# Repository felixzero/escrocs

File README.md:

# Repository of the E.S.C.Ro.C.S. team at the French robotics cup

We have participated in 2020, 2021 and 2022.

You can find here our codes, PCB and mechanical designs. We use Platform.io and VSCodium for coding, KiCAD for PCB CAD and either FreeCAD or TinkerCAD for mechanical design.

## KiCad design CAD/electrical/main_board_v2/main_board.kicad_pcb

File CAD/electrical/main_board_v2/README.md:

# Main board

This is the brain of our robots. It is based on a single ESP32 chip executing the strategy and interfacing with other boards.

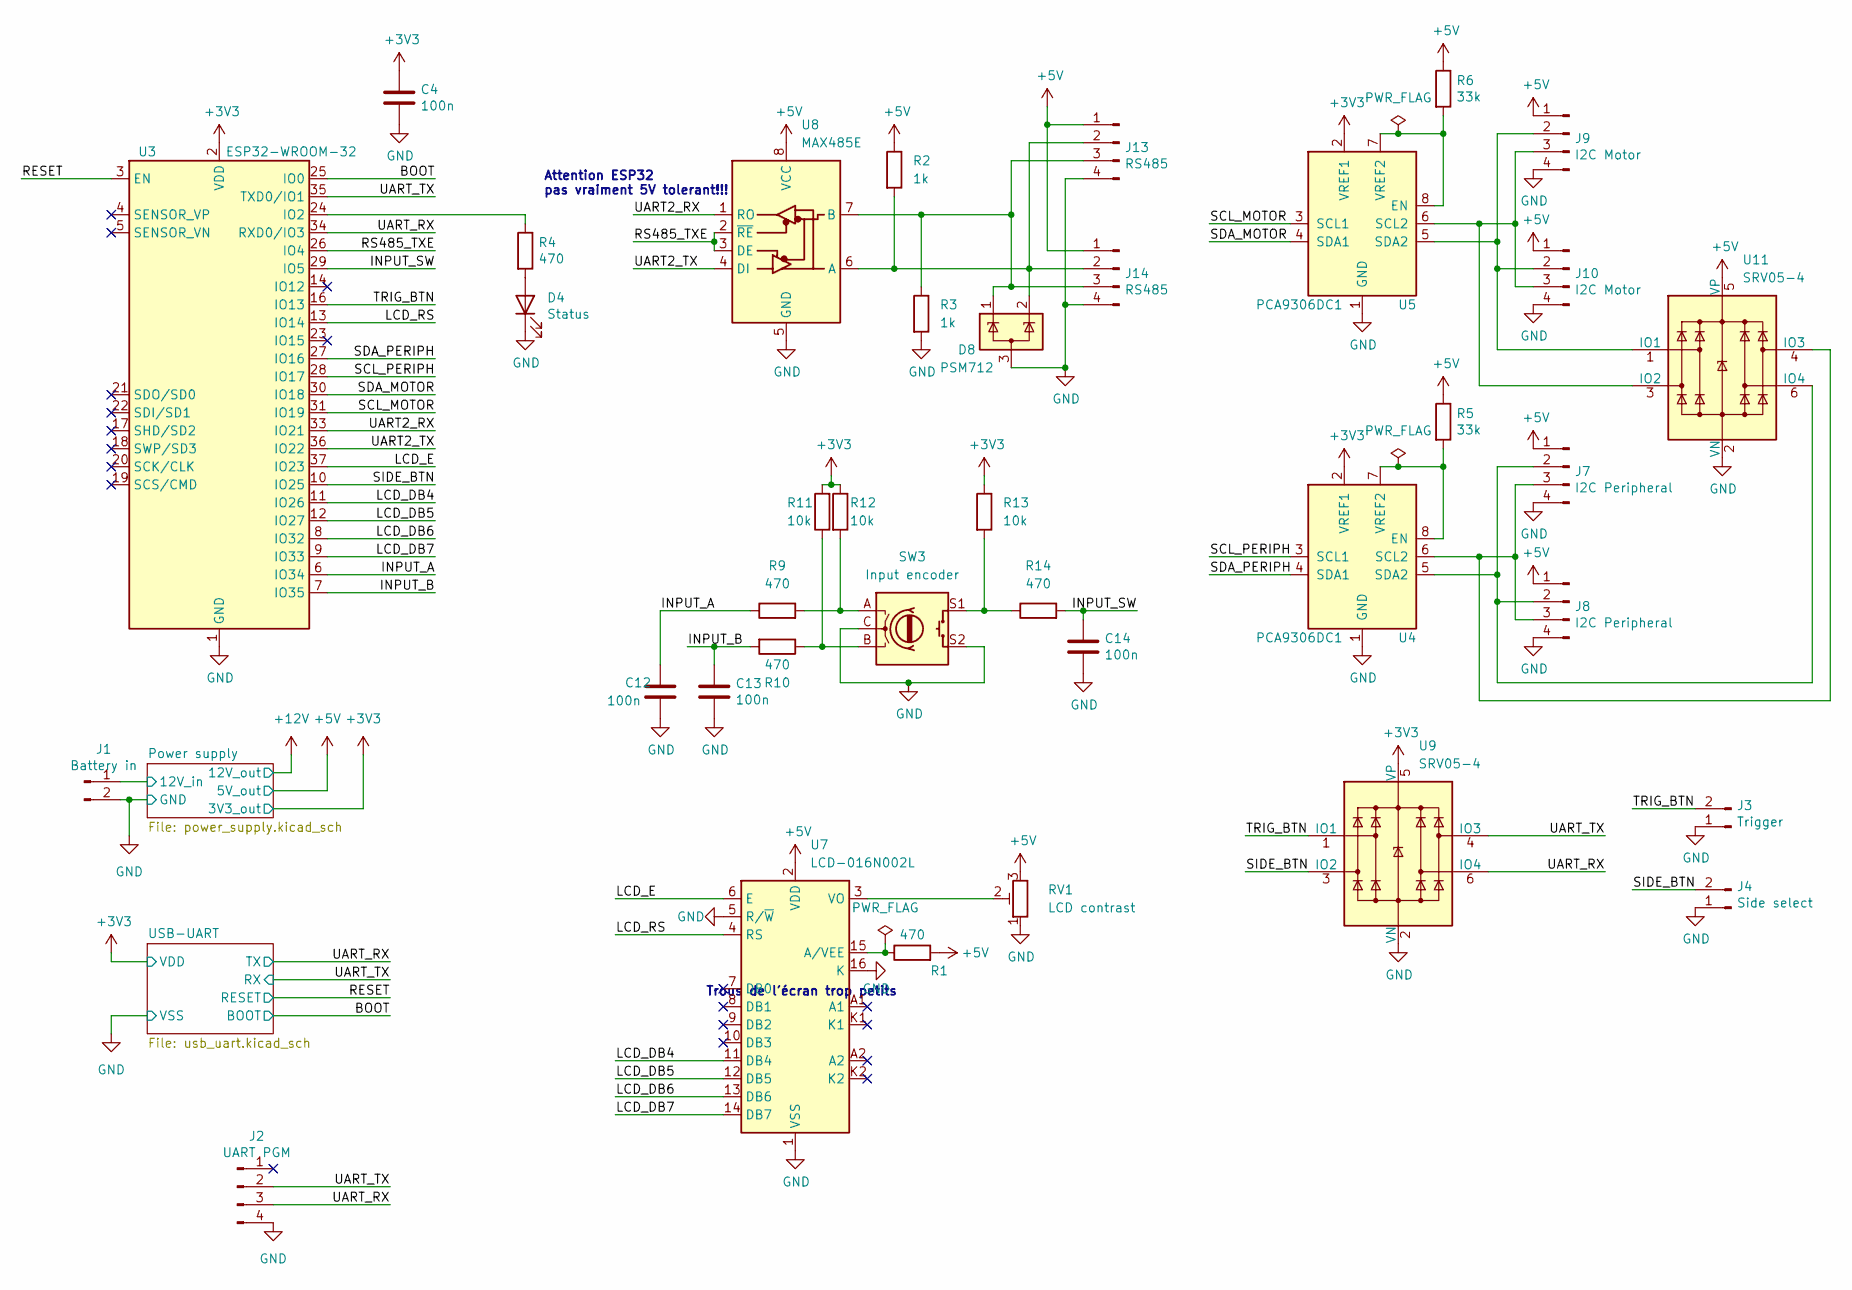
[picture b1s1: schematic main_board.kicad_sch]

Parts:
C4, C12, C13, C14: 100n; C_0805_2012Metric; LCSC C28233
D4: Status; LED_0603_1608Metric; LCSC C2286
D8: PSM712; SOT-23
J1: Battery in; BarrelJack_Horizontal
J2: UART PGM; Molex_KK-254_AE-6410-04A_1x04_P2.54mm_Vertical
J3: Trigger; Molex_KK-254_AE-6410-02A_1x02_P2.54mm_Vertical
J4: Side select; Molex_KK-254_AE-6410-02A_1x02_P2.54mm_Vertical
J7, J8: I2C Peripheral; Molex_KK-254_AE-6410-04A_1x04_P2.54mm_Vertical
J9, J10: I2C Motor; Molex_KK-254_AE-6410-04A_1x04_P2.54mm_Vertical
J13, J14: RS485; Molex_KK-254_AE-6410-04A_1x04_P2.54mm_Vertical
R1: 470; R_1206_3216Metric
R2: 1k; R_0603_1608Metric; LCSC C20190
R3: 1k; R_0603_1608Metric; LCSC C20192
R4: 470; R_1206_3216Metric; LCSC C17901
R5, R6: 33k; R_0603_1608Metric; LCSC C17900
R9, R10, R14: 470; R_0603_1608Metric
R11, R12, R13: 10k; R_0603_1608Metric
RV1: LCD contrast; Potentiometer_Bourns_3314J_Vertical
SW3: Input encoder; RotaryEncoder_Alps_EC11E-Switch_Vertical_H20mm
U3: ESP32-WROOM-32; ESP32-WROOM-32U; LCSC C82899
U4, U5: PCA9306DC1; VSSOP-8_2.3x2mm_P0.5mm
U7: LCD-016N002L; WC1602A
U8: MAX485E; SOIC-8_3.9x4.9mm_P1.27mm
U9, U11: SRV05-4; SOT-23-6

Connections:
+3V3: C4.1, R11.2, R12.1, R13.1, U3.2 (VDD), U4.2 (VREF1), U5.2 (VREF1), U9.5 (VP); also elsewhere on the board
+5V: J7.1, J8.1, J9.1, J10.1, J13.1, J14.1, R1.2, R2.1, R5.1, R6.1, RV1.3, U7.2 (VDD), U8.8 (VCC), U11.5 (VP); also elsewhere on the board
/BOOT: U3.25 (IO0); also elsewhere on the board
/INPUT_A: C12.1, R9.1, U3.6 (IO34)
/INPUT_B: C13.1, R10.2, U3.7 (IO35)
/INPUT_SW: C14.1, R14.2, U3.29 (IO5)
/LCD_DB4: U3.11 (IO26), U7.11 (DB4)
/LCD_DB5: U3.12 (IO27), U7.12 (DB5)
/LCD_DB6: U3.8 (IO32), U7.13 (DB6)
/LCD_DB7: U3.9 (IO33), U7.14 (DB7)
/LCD_E: U3.37 (IO23), U7.6 (E)
/LCD_RS: U3.13 (IO14), U7.4 (RS)
/Power supply/12V_in: J1.1; also elsewhere on the board
/RESET: U3.3 (EN); also elsewhere on the board
/RS485_TXE: U3.26 (IO4), U8.2 (~RE), U8.3 (DE)
/SCL_MOTOR: U3.31 (IO19), U5.3 (SCL1)
/SCL_PERIPH: U3.28 (IO17), U4.3 (SCL1)
/SDA_MOTOR: U3.30 (IO18), U5.4 (SDA1)
/SDA_PERIPH: U3.27 (IO16), U4.4 (SDA1)
/SIDE_BTN: J4.2, U3.10 (IO25), U9.3 (IO2)
/TRIG_BTN: J3.2, U3.16 (IO13), U9.1 (IO1)
/UART2_RX: U3.33 (IO21), U8.1 (RO)
/UART2_TX: U3.36 (IO22), U8.4 (DI)
/UART_RX: J2.3, U3.34 (RXD0/IO3), U9.6 (IO4); also elsewhere on the board
/UART_TX: J2.2, U3.35 (TXD0/IO1), U9.4 (IO3); also elsewhere on the board
GND: C4.2, C12.2, C13.2, C14.2, D4.1 (K), D8.3 (A), J1.2, J2.4, J3.1, J4.1, J7.4, J8.4, J9.4, J10.4, J13.4, J14.4, R3.2, RV1.1, SW3.C, SW3.S2, U3.1 (GND), U3.15 (GND), U3.38 (GND), U3.39 (GND), U4.1 (GND), U5.1 (GND), U7.1 (VSS), U7.5 (R/~W), U7.16 (K), U8.5 (GND), U9.2 (VN), U11.2 (VN); also elsewhere on the board
unnamed: D4.2 (A), R4.2
unnamed: J7.2, J8.2, U4.5 (SDA2), U11.6 (IO4)
unnamed: J7.3, J8.3, U4.6 (SCL2), U11.4 (IO3)
unnamed: J9.2, J10.2, U5.5 (SDA2), U11.1 (IO1)
unnamed: J9.3, J10.3, U5.6 (SCL2), U11.3 (IO2)
unnamed: R1.1, U7.15 (A/VEE)
unnamed: R4.1, U3.24 (IO2)
unnamed: R5.2, U4.7 (VREF2), U4.8 (EN)
unnamed: R6.2, U5.7 (VREF2), U5.8 (EN)
unnamed: R10.1, R11.1, SW3.B
unnamed: R9.2, R12.2, SW3.A
unnamed: R13.2, R14.1, SW3.S1
unnamed: RV1.2, U7.3 (VO)
unnamed: D8.2 (K), J13.2, J14.2, R2.2, U8.6 (A)
unnamed: D8.1 (K), J13.3, J14.3, R3.1, U8.7 (B)

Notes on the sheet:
Attention ESP32 pas vraiment 5V tolerant!!!
Trous de l'écran trop petits

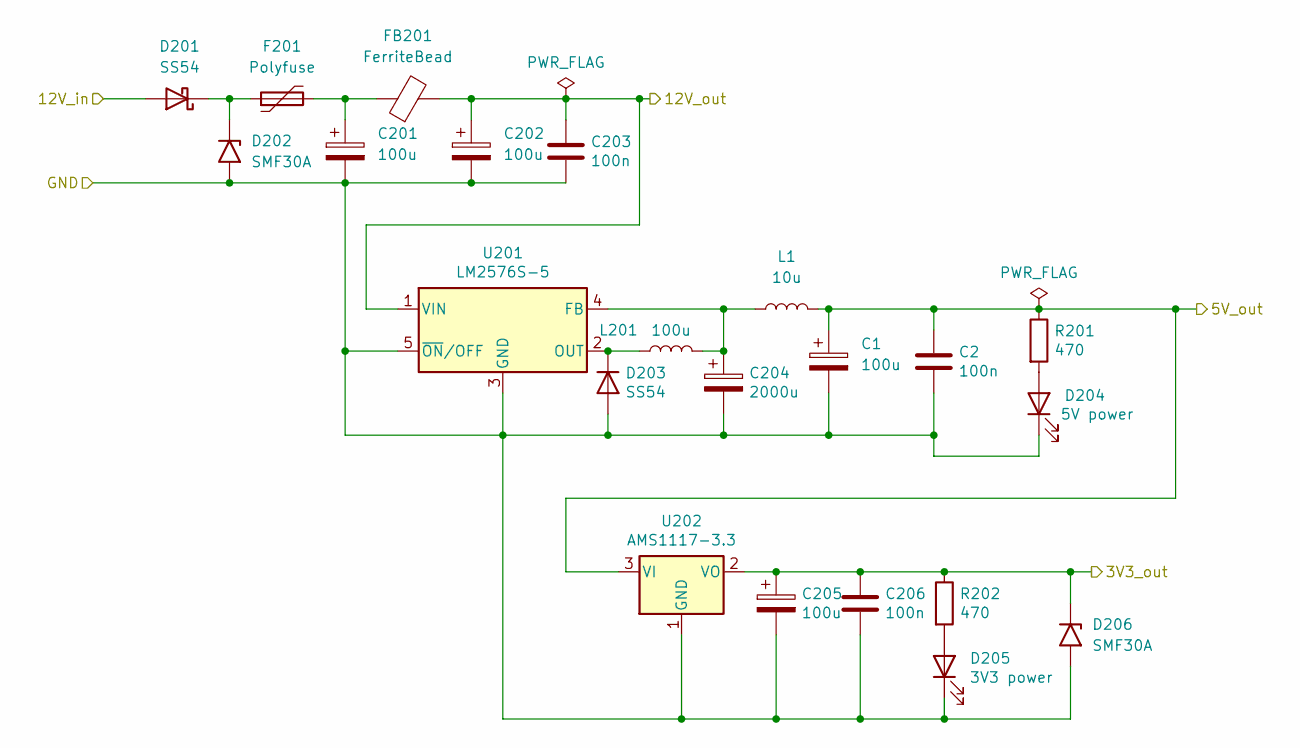
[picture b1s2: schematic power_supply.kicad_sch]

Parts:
C1, C201, C202, C205: 100u; CP_Elec_8x10; LCSC C16133
C2, C203, C206: 100n; C_0805_2012Metric; LCSC C28233
C204: 2000u; CP_Elec_10x10.5; LCSC C10752
D201: SS54; D_SMA
D202, D206: SMF30A; D_SMF; LCSC C19077518
D203: SS54; D_SMA; LCSC C22452
D204: 5V power; LED_0603_1608Metric; LCSC C2286
D205: 3V3 power; LED_0603_1608Metric; LCSC C2286
F201: Polyfuse; Fuse_1812_4532Metric
FB201: FerriteBead; L_0805_2012Metric
L1: 10u; L_12x12mm_H6mm
L201: 100u; L_12x12mm_H6mm; LCSC C169378
R201: 470; R_1206_3216Metric; LCSC C17887
R202: 470; R_1206_3216Metric; LCSC C17901
U201: LM2576S-5; TO-263-5_TabPin3; LCSC C34465
U202: AMS1117-3.3; SOT-223-3_TabPin2; LCSC C6186

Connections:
+3V3: C205.1, C206.1, D206.1 (A1), R202.1, U202.2 (VO); also elsewhere on the board
+5V: C1.1, C2.1, L1.2, R201.1, U202.3 (VI); also elsewhere on the board
+12V: C202.1, C203.1, FB201.2, U201.1 (VIN)
/Power supply/12V_in: D201.2 (A); also elsewhere on the board
GND: C1.2, C2.2, C201.2, C202.2, C203.2, C204.2, C205.2, C206.2, D202.2 (A2), D203.2 (A), D204.1 (K), D205.1 (K), D206.2 (A2), U201.3 (GND), U201.5 (~ON/OFF), U202.1 (GND); also elsewhere on the board
unnamed: C201.1, F201.2, FB201.1
unnamed: C204.1, L1.1, L201.2, U201.4 (FB)
unnamed: D201.1 (K), D202.1 (A1), F201.1
unnamed: D203.1 (K), L201.1, U201.2 (OUT)
unnamed: D204.2 (A), R201.2
unnamed: D205.2 (A), R202.2

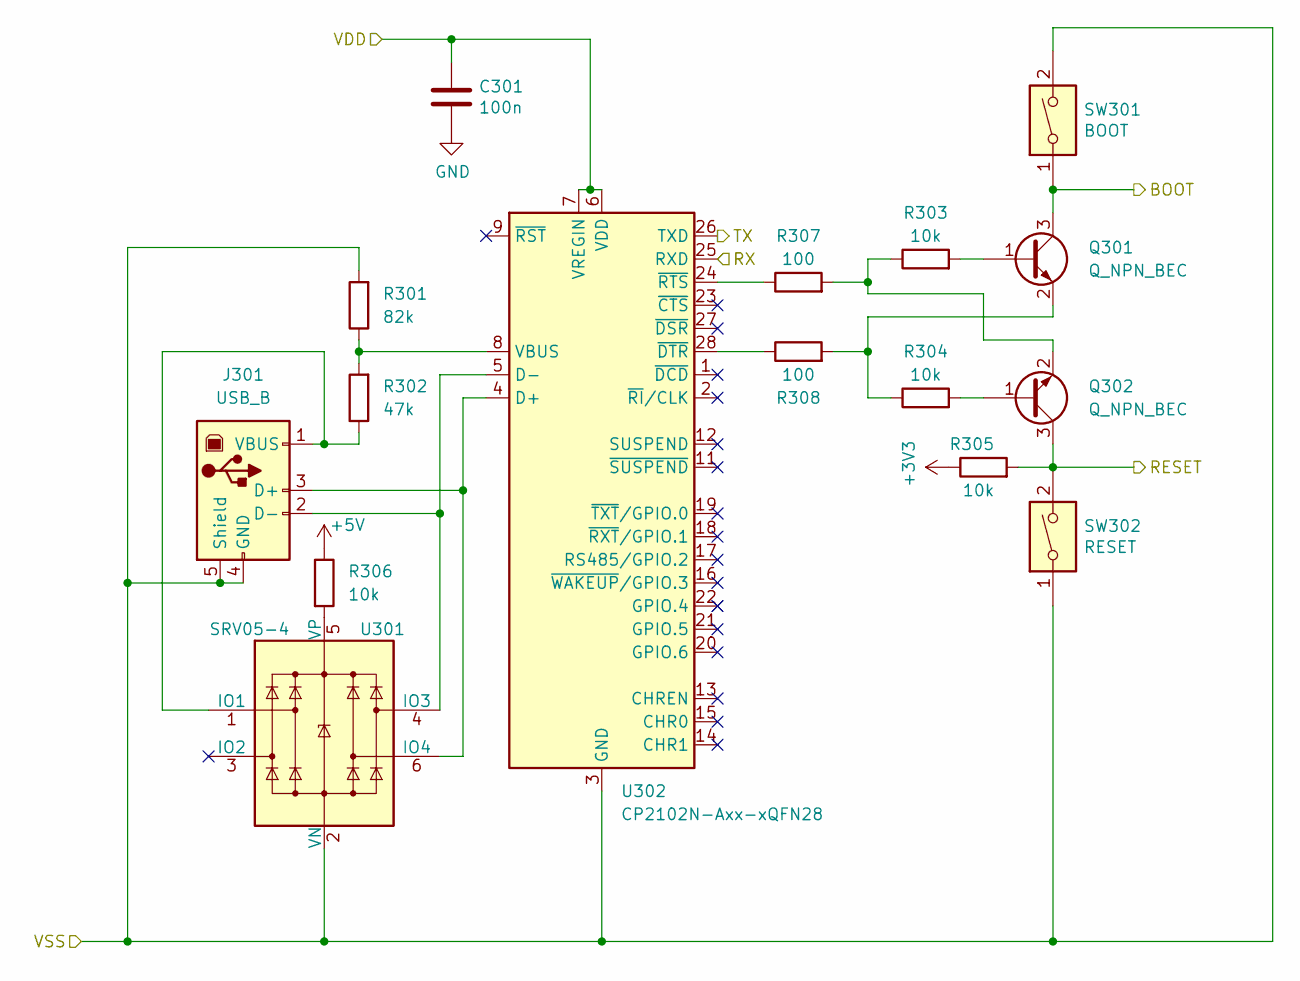
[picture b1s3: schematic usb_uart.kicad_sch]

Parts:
C301: 100n; C_0805_2012Metric; LCSC C28233
J301: USB_B; USB_B_TE_5787834_Vertical
Q301, Q302: Q_NPN_BEC; SOT-23
R301: 82k; R_0603_1608Metric
R302: 47k; R_0603_1608Metric
R303, R304, R306: 10k; R_0603_1608Metric
R305: 10k; R_0603_1608Metric; LCSC C17902
R307, R308: 100; R_0603_1608Metric; LCSC C22775
SW301: BOOT; SW_Push_1P1T_NO_6x6mm_H9.5mm
SW302: RESET; SW_Push_1P1T_NO_6x6mm_H9.5mm
U301: SRV05-4; SOT-23-6
U302: CP2102N-Axx-xQFN28; QFN-28-1EP_5x5mm_P0.5mm_EP3.35x3.35mm

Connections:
+3V3: C301.1, R305.1, U302.6 (VDD), U302.7 (VREGIN); also elsewhere on the board
+5V: R306.1; also elsewhere on the board
/BOOT: Q301.3 (C), SW301.1; also elsewhere on the board
/RESET: Q302.3 (C), R305.2, SW302.2; also elsewhere on the board
/UART_RX: U302.26 (TXD); also elsewhere on the board
/UART_TX: U302.25 (RXD); also elsewhere on the board
GND: C301.2, J301.4 (GND), J301.5 (Shield), R301.2, SW301.2, SW302.1, U301.2 (VN), U302.3 (GND), U302.29 (GND); also elsewhere on the board
unnamed: J301.1 (VBUS), R302.1, U301.1 (IO1)
unnamed: J301.2 (D-), U301.4 (IO3), U302.5 (D-)
unnamed: J301.3 (D+), U301.6 (IO4), U302.4 (D+)
unnamed: Q301.1 (B), R303.2
unnamed: Q301.2 (E), R304.1, R308.2
unnamed: Q302.1 (B), R304.2
unnamed: Q302.2 (E), R303.1, R307.2
unnamed: R301.1, R302.2, U302.8 (VBUS)
unnamed: R306.2, U301.5 (VP)
unnamed: R307.1, U302.24 (~RTS)
unnamed: R308.1, U302.28 (~DTR)

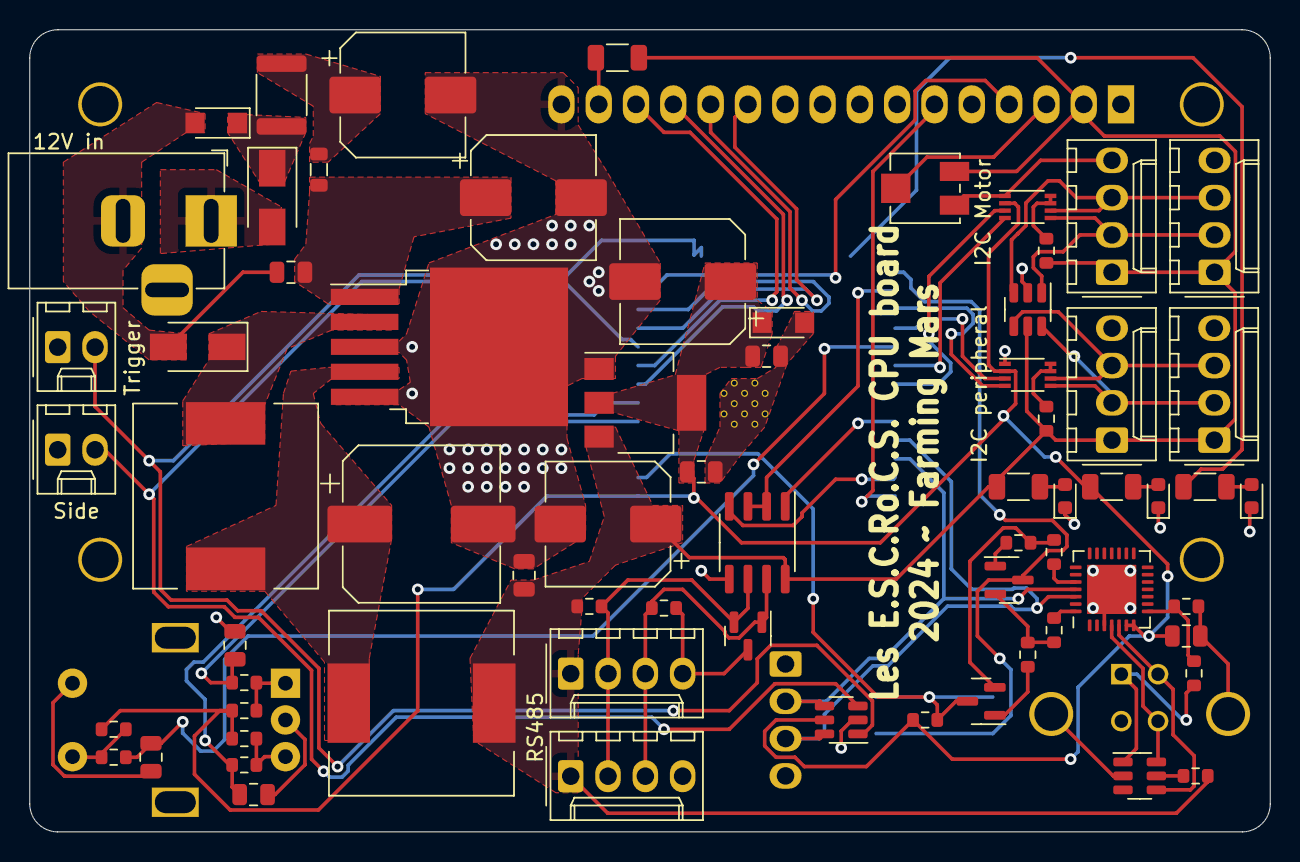
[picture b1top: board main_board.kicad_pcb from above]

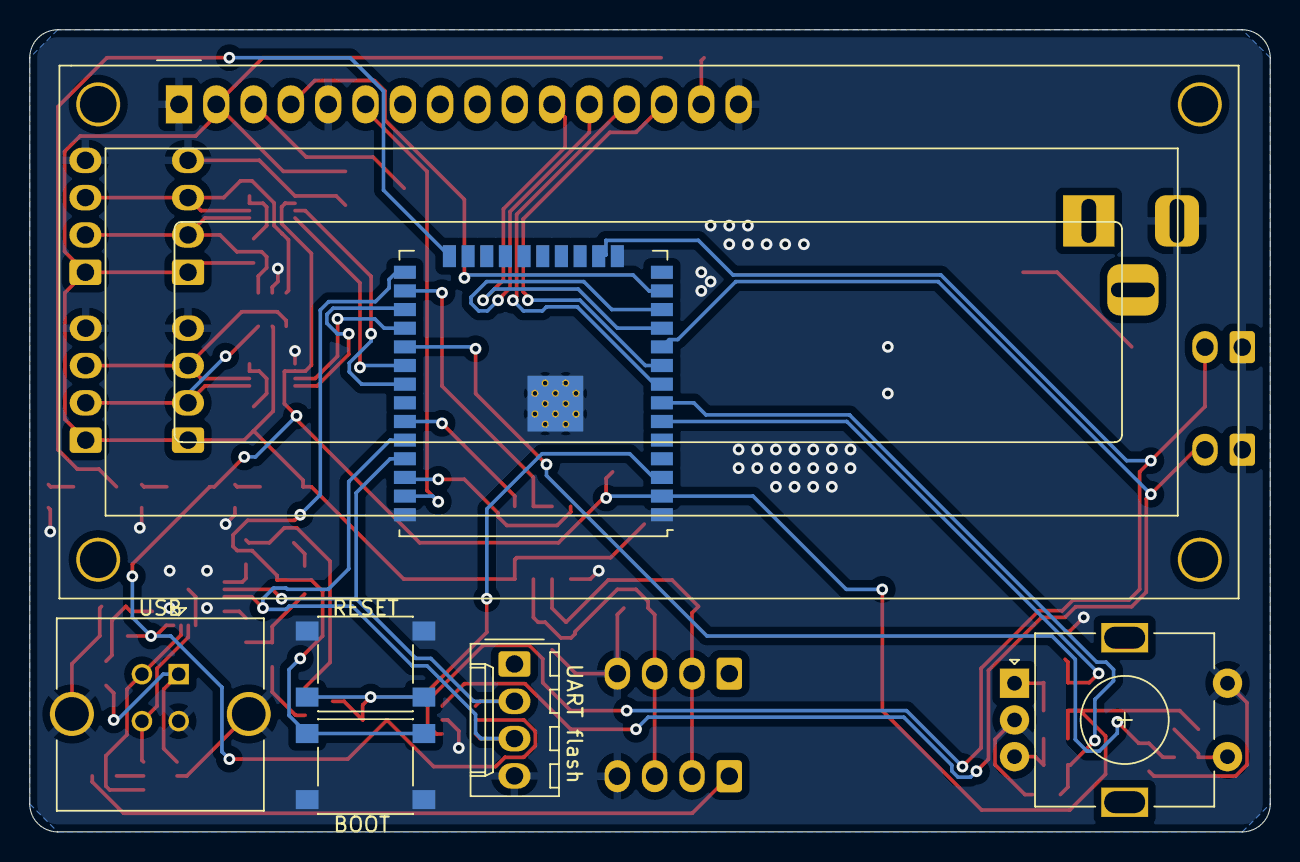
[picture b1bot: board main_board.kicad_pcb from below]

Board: 2 copper layers, 84.5 x 54.6 mm, 75 parts (7 on the bottom side), 59 nets.

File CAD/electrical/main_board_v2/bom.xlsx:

Comment | Designator | Footprint | LCSC part number
100n capacitor | C2,C4,C12,C13,C14,C203,C206,C301 | Capacitor_SMD:C_0805_2012Metric | C28233
100u capacitor | C1,C201,C202,C205 | Capacitor_SMD:CP_Elec_8x10 | C294509
2000u capacitor | C204 | Capacitor_SMD:CP_Elec_10x10.5 | C336751
LED | D4,D204,D205 | LED_SMD:LED_0603_1608Metric | C72038
PSM712 | D8 | Package_TO_SOT_SMD:SOT-23 | C32677
SS54 | D201,D203 | Diode_SMD:D_SMA | C22452
SMF30A | D202,D206 | Diode_SMD:D_SMF | C2990493
Polyfuse RF1404-000 | F201 | Fuse:Fuse_1812_4532Metric | C3107
GZ2012D601TF | FB201 | Inductor_SMD:L_0805_2012Metric | C1017
100u inductor | L201 | Inductor_SMD:L_12x12mm_H6mm | C169378
10u inductor | L1 | Inductor_SMD:L_12x12mm_H6mm | C9904
Basic NPN | Q301,Q302 | Package_TO_SOT_SMD:SOT-23 | C20526
470 resistor | R1,R4,R201,R202,R9,R10,R14 | Resistor_SMD:R_1206_3216Metric | C23179
33k resistor | R5,R6 | Resistor_SMD:R_0603_1608Metric | C4216
10k resistor | R11,R12,R13,R303,R304,R305,R306 | Resistor_SMD:R_0603_1608Metric | C25804
82k resistor | R301 | Resistor_SMD:R_0603_1608Metric | C23254
47k resistor | R302 | Resistor_SMD:R_0603_1608Metric | C25819
100 resistor | R307,R308 | Resistor_SMD:R_0603_1608Metric | C22775
1k resistor | R2,R3 | Resistor_SMD:R_0603_1608Metric | C22775
PCA9306DC | U4,U5 | Package_SO:VSSOP-8_2.3x2mm_P0.5mm | C129510
SN75176BDR | U8 | Package_SO:SOIC-8_3.9x4.9mm_P1.27mm | C7063
SRV05-4 | U9,U11,U301 | Package_TO_SOT_SMD:SOT-23-6 | C85364
LM2576S-5 | U201 | Package_TO_SOT_SMD:TO-263-5_TabPin3 | C34465
AMS1117-3.3 | U202 | Package_TO_SOT_SMD:SOT-223-3_TabPin2 | C6186
CP2102 | U302 | Package_DFN_QFN:QFN-28-1EP_5x5mm_P0.5mm_EP3.35x3.35mm | C6568
2kO potentiometer | RV1 | Potentiometer_SMD:Potentiometer_Bourns_3314J_Vertical | C94513

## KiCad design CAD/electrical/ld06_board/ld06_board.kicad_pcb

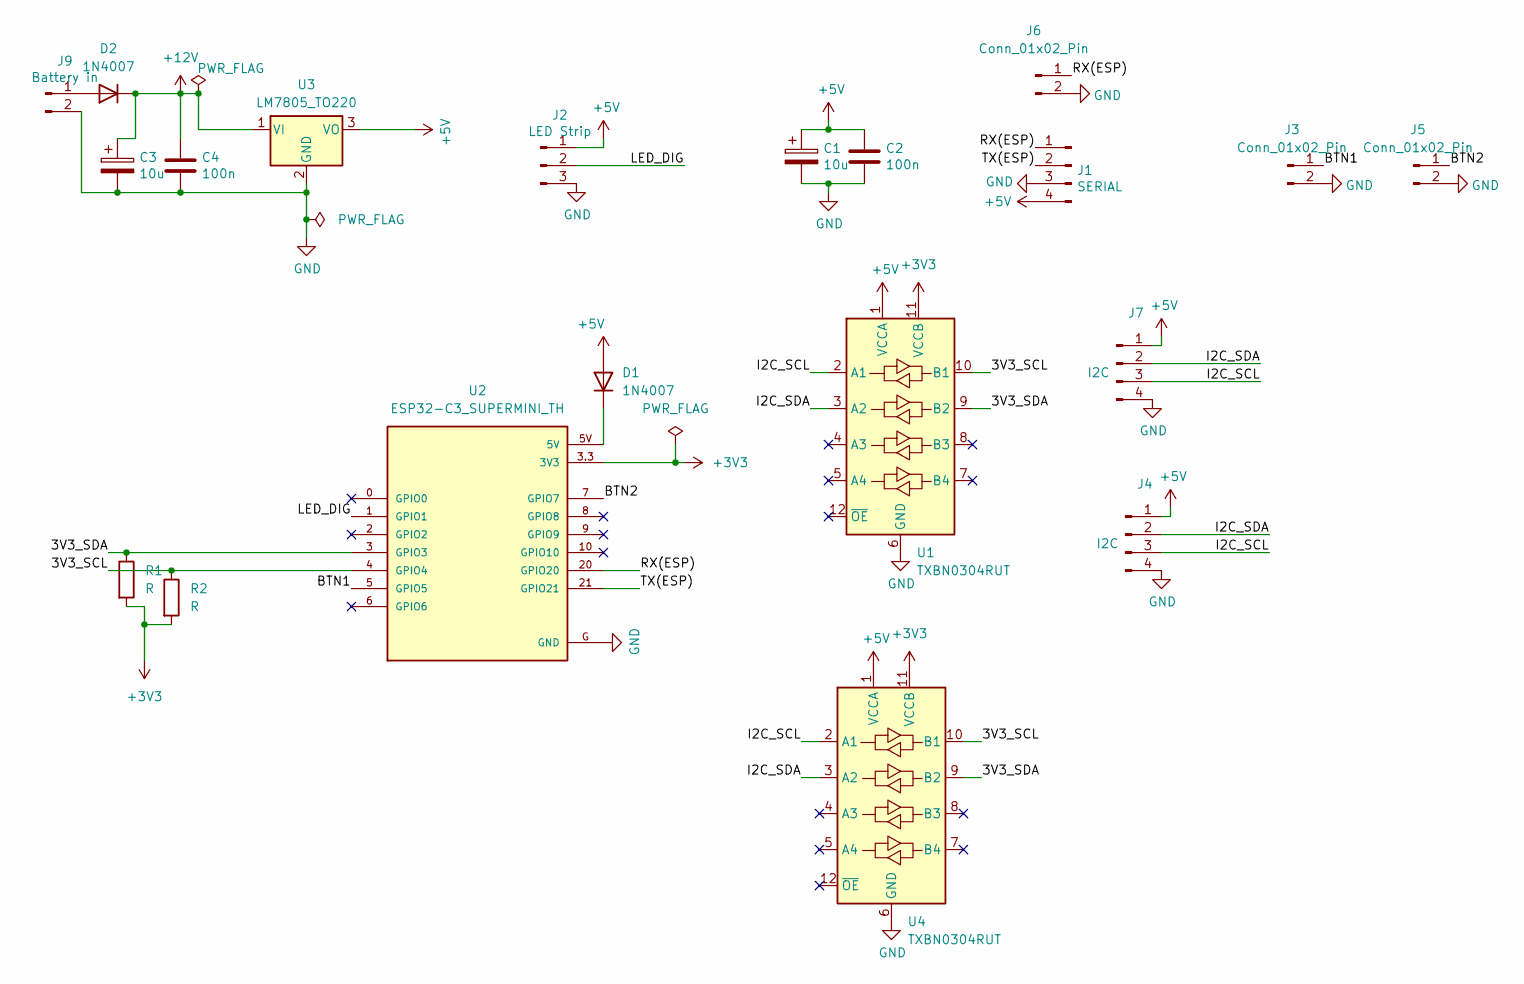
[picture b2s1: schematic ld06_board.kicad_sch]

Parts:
C1, C3: 10u; CP_Radial_D8.0mm_P3.80mm
C2, C4: 100n; R_Axial_DIN0204_L3.6mm_D1.6mm_P5.08mm_Vertical
D1, D2: 1N4007; D_T-1_P12.70mm_Horizontal
J1: SERIAL; Molex_KK-254_AE-6410-04A_1x04_P2.54mm_Vertical
J2: LED Strip; Molex_KK-254_AE-6410-03A_1x03_P2.54mm_Vertical
J3, J5, J6: Conn_01x02_Pin; Molex_KK-254_AE-6410-02A_1x02_P2.54mm_Vertical
J4, J7: I2C; Molex_KK-254_AE-6410-04A_1x04_P2.54mm_Vertical
J9: Battery in; BarrelJack_Horizontal
R1, R2: R; R_Axial_DIN0309_L9.0mm_D3.2mm_P12.70mm_Horizontal
U1: TXBN0304RUT; I2C_ali_level_shifter
U2: ESP32-C3_SUPERMINI_TH; MODULE_ESP32-C3_SUPERMINI
U3: LM7805_TO220; TO-220-3_Vertical
U4: TXBN0304RUT; PCA9306_ali

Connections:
+3V3: R1.2, R2.2, U1.11 (VCCB), U2.3.3 (3V3), U4.11 (VCCB)
+5V: C1.1, C2.1, D1.2 (A), J1.4, J2.1, J4.1, J7.1, U1.1 (VCCA), U3.3 (VO), U4.1 (VCCA)
+12V: C3.1, C4.1, D2.1 (K), U3.1 (VI)
/3V3_SCL: R2.1, U1.10 (B1), U2.4 (GPIO4), U4.10 (B1)
/3V3_SDA: R1.1, U1.9 (B2), U2.3 (GPIO3), U4.9 (B2)
/BTN1: J3.1, U2.5 (GPIO5); also elsewhere on the board
/BTN2: J5.1, U2.7 (GPIO7); also elsewhere on the board
/I2C_SCL: J4.3, J7.3, U1.2 (A1), U4.2 (A1)
/I2C_SDA: J4.2, J7.2, U1.3 (A2), U4.3 (A2)
/LED_DIG: J2.2, U2.1 (GPIO1)
/RX(ESP): J1.1, J6.1, U2.20 (GPIO20)
/TX(ESP): J1.2, U2.21 (GPIO21)
GND: C1.2, C2.2, C3.2, C4.2, J1.3, J2.3, J3.2, J4.4, J5.2, J6.2, J7.4, J9.2, U1.6 (GND), U2.G (GND), U3.2 (GND), U4.6 (GND); also elsewhere on the board
unnamed: D1.1 (K), U2.5V
unnamed: D2.2 (A), J9.1

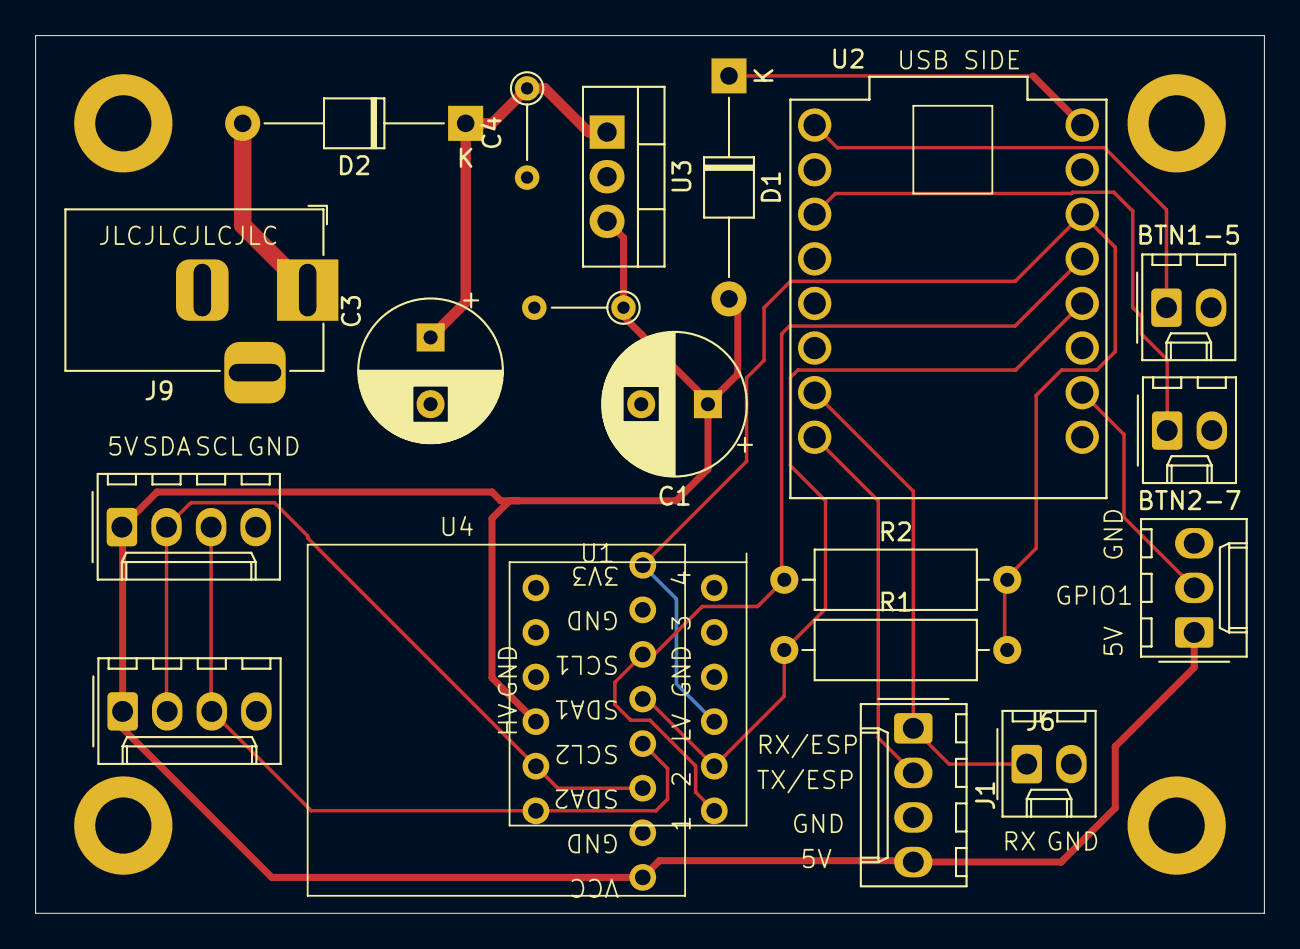
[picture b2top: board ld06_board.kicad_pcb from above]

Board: 2 copper layers, 70.0 x 50.0 mm, 20 parts (0 on the bottom side), 15 nets.

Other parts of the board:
BTN1-5, BTN2-7: Conn_01x02_Pin; Molex_KK-254_AE-6410-02A_1x02_P2.54mm_Vertical

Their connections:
/BTN1: BTN1-5.1; also elsewhere on the board
/BTN2: BTN2-7.1; also elsewhere on the board
GND: BTN1-5.2, BTN2-7.2; also elsewhere on the board

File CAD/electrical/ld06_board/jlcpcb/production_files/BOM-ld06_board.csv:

Comment,Designator,Footprint,LCSC,Quantity
R,R2,R_Axial_DIN0309_L9.0mm_D3.2mm_P12.70mm_Horizontal,,1
TXBN0304RUT,U1,I2C_ali_level_shifter,,1
Conn_01x02_Pin,BTN1-5,Molex_KK-254_AE-6410-02A_1x02_P2.54mm_Vertical,,1
100n,C4,R_Axial_DIN0204_L3.6mm_D1.6mm_P5.08mm_Vertical,,1
Conn_01x02_Pin,BTN2-7,Molex_KK-254_AE-6410-02A_1x02_P2.54mm_Vertical,,1
Conn_01x02_Pin,J6,Molex_KK-254_AE-6410-02A_1x02_P2.54mm_Vertical,,1
SERIAL,J1,Molex_KK-254_AE-6410-04A_1x04_P2.54mm_Vertical,,1
TXBN0304RUT,U4,PCA9306_ali,,1
1N4007,D1,D_T-1_P12.70mm_Horizontal,,1
100n,C2,R_Axial_DIN0204_L3.6mm_D1.6mm_P5.08mm_Vertical,,1
10u,C3,CP_Radial_D8.0mm_P3.80mm,,1
I2C,J4,Molex_KK-254_AE-6410-04A_1x04_P2.54mm_Vertical,,1
ESP32-C3_SUPERMINI_TH,U2,MODULE_ESP32-C3_SUPERMINI,,1
LM7805_TO220,U3,TO-220-3_Vertical,,1
I2C,J7,Molex_KK-254_AE-6410-04A_1x04_P2.54mm_Vertical,,1
LED Strip,J2,Molex_KK-254_AE-6410-03A_1x03_P2.54mm_Vertical,,1
10u,C1,CP_Radial_D8.0mm_P3.80mm,,1
1N4007,D2,D_T-1_P12.70mm_Horizontal,,1
R,R1,R_Axial_DIN0309_L9.0mm_D3.2mm_P12.70mm_Horizontal,,1
Battery in,J9,BarrelJack_Horizontal,,1

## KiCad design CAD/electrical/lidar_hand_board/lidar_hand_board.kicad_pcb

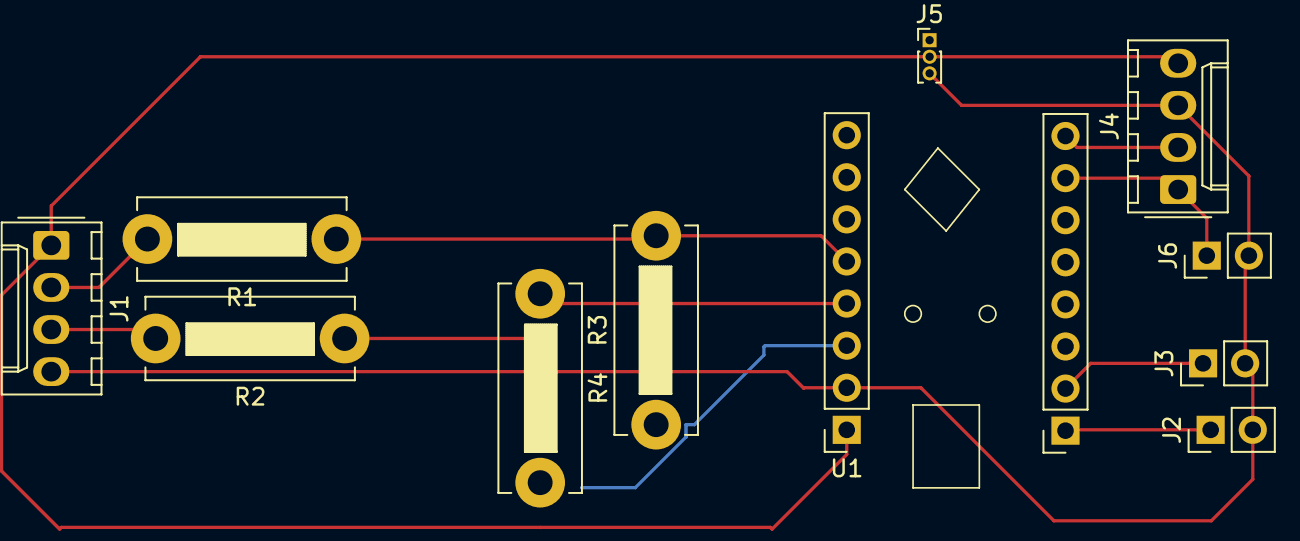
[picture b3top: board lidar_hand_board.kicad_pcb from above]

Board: 2 copper layers, 11 parts (0 on the bottom side), 11 nets.

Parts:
J1: I2C; Molex_KK-254_AE-6410-04A_1x04_P2.54mm_Vertical
J2, J3, J6: Conn_01x02_Pin; PinHeader_1x02_P2.54mm_Vertical
J4: SERIAL; Molex_KK-254_AE-6410-04A_1x04_P2.54mm_Vertical
J5: Conn_01x03_Pin; PinHeader_1x03_P1.00mm_Vertical
R1, R2: 100; R_Bare_Metal_Element_L12.4mm_W4.8mm_P11.40mm
R3, R4: 1000; R_Bare_Metal_Element_L12.4mm_W4.8mm_P11.40mm
U1: ESP32-S3; ESP32_C3_MINI_aproximative_footprint

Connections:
+5V: J1.1, J4.4, J5.2, R3.1, R4.2, U1.2 (VDD3P3)
/BTN1: J2.1, U1.10 (GPIO5)
/BTN2: J3.1, U1.11 (GPIO6)
/LED: J5.1, U1.6 (GPIO1)
/RX(ESP): J4.1, J6.1, U1.26 (GPIO20/USB_D+)
/SCL: R2.1, R4.1, U1.9 (GPIO4)
/SDA: R1.1, R3.2, U1.8 (GPIO3)
/TX(ESP): J4.2, U1.27 (GPIO21)
GND: J1.4, J2.2, J3.2, J4.3, J5.3, J6.2, U1.57 (GND)
unnamed: J1.2, R1.2
unnamed: J1.3, R2.2

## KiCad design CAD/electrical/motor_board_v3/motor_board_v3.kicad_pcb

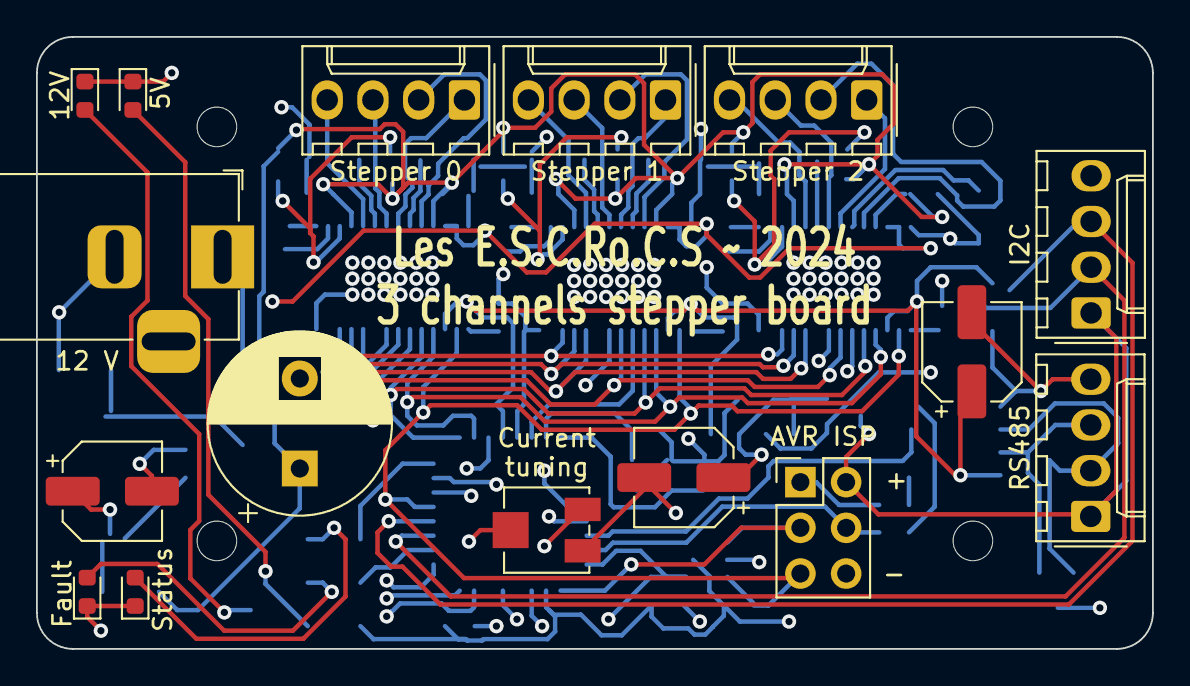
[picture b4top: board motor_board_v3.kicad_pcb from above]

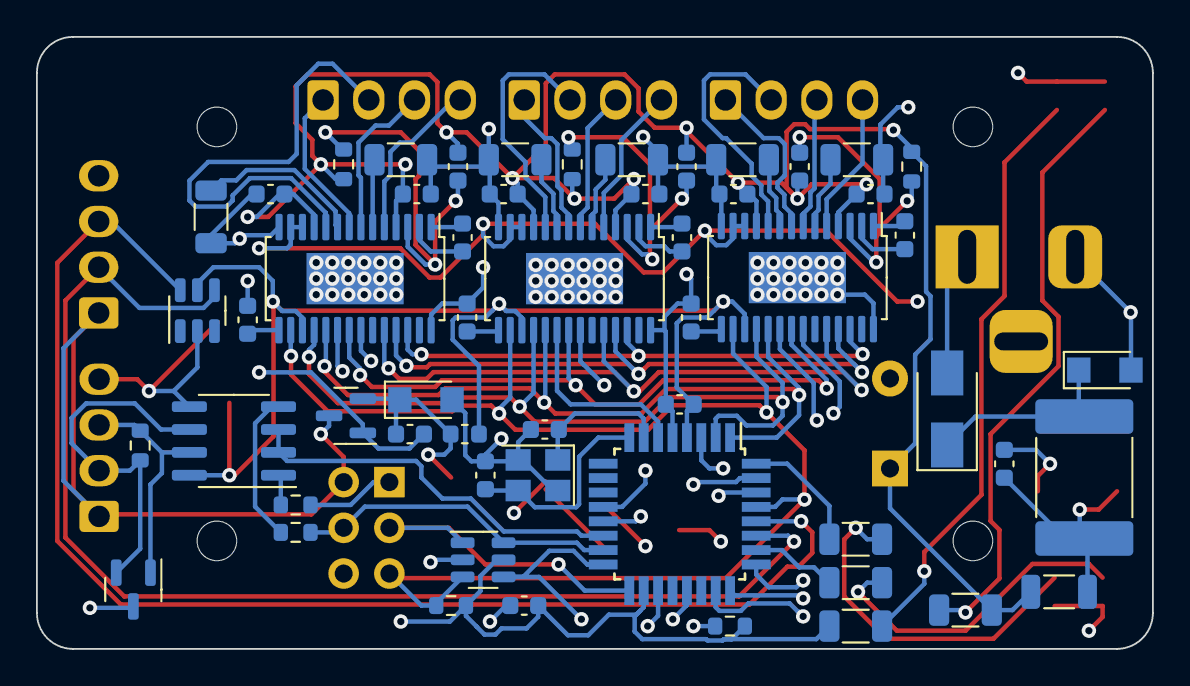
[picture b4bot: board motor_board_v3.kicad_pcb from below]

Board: 4 copper layers, 62.0 x 34.0 mm, 71 parts (55 on the bottom side), 71 nets.

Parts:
C1, C2, C4, C6, C8, C9, C10, C14, C15, C16, C20, C21, C22: 100n; C_0603_1608Metric
C3, C5, C31: 10u; CP_Elec_5x5.4
C7, C13, C19: 10n 50V; C_0603_1608Metric
C11, C17: 22p; C_0603_1608Metric
C12, C18, C24: 0.47u; C_0603_1608Metric
C30: 100u; CP_Radial_D10.0mm_P5.00mm
D1: Fault; LED_0603_1608Metric
D2: ST; LED_0603_1608Metric
D3: 5V; LED_0603_1608Metric
D5: SS54; D_SMA
D6, D7: SMF30A; D_SMF
D8: 12V; LED_0603_1608Metric
D9: PSM712; SOT-23
F1: 2920L700SLPR; Fuse_2920_7451Metric
FB1: BLM31PG330SZ1L; L_1206_3216Metric
FB2: GZ1608D601TF; L_0603_1608Metric
J1: AVR-ISP-6; PinHeader_2x03_P2.54mm_Vertical
J2: 12V; BarrelJack_Horizontal
J3: I2C; Molex_KK-254_AE-6410-04A_1x04_P2.54mm_Vertical
J4: RS485; Molex_KK-254_AE-6410-04A_1x04_P2.54mm_Vertical
J5, J6, J7: Stepper; Molex_KK-254_AE-6410-04A_1x04_P2.54mm_Vertical
Q1: SI2301CDS-T1-GE3; SOT-23
R1, R4, R6, R7: 470; R_1206_3216Metric
R2, R3: 330; R_0603_1608Metric
R5: 120R; R_0603_1608Metric
R9, R12, R15: 1M; R_0603_1608Metric
R10, R11, R13, R14, R16, R17: 0.1; R_1206_3216Metric
R18, R19: 10k; R_0603_1608Metric
RV1: 4.7k; Potentiometer_Bourns_3314J_Vertical
U1: ATmega328PB-A; TQFP-32_7x7mm_P0.8mm
U2: MAX485E; SOIC-8_3.9x4.9mm_P1.27mm
U3, U4, U5: DRV8825; HTSSOP-28-1EP_4.4x9.7mm_P0.65mm_EP2.85x5.4mm
U6, U8: SRV05-4; SOT-23-6
Y1: 16MHz; Crystal_SMD_3225-4Pin_3.2x2.5mm

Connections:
+5V: C1.1, C2.1, C31.1, FB2.2, R7.1, R18.1, R19.1, U1.4 (VCC), U1.18 (AVCC), U2.8 (VCC), U3.17 (nSLEEP), U4.17 (nSLEEP), U5.17 (nSLEEP), U6.5 (VP), U8.5 (VP)
+12V: C8.2, C9.1, C10.1, C14.2, C15.1, C16.1, C20.2, C21.1, C22.1, C30.1, FB1.2, R1.1, R9.2, R12.2, R15.2, U3.4 (VMA), U3.11 (VMB), U4.4 (VMA), U4.11 (VMB), U5.4 (VMA), U5.11 (VMB)
/DECAY: U1.1 (PD3), U3.19 (DECAY), U4.19 (DECAY), U5.19 (DECAY)
/DIR0: U1.3 (PE0), U3.20 (DIR)
/DIR1: U1.6 (PE1), U4.20 (DIR)
/DIR2: U1.19 (PE2), U5.20 (DIR)
/FAULT: U1.2 (PD4), U3.18 (nFAULT), U4.18 (nFAULT), U5.18 (nFAULT)
/FAULT_ST: R4.1, U1.26 (PC3)
/I2C_SCL: J3.3, U1.28 (PC5), U8.6 (IO4)
/I2C_SDA: J3.2, U1.27 (PC4), U8.4 (IO3)
/MODE0: U1.23 (PC0), U3.24 (MODE0), U4.24 (MODE0), U5.24 (MODE0)
/MODE1: U1.24 (PC1), U3.25 (MODE1), U4.25 (MODE1), U5.25 (MODE1)
/MODE2: U1.25 (PC2), U3.26 (MODE2), U4.26 (MODE2), U5.26 (MODE2)
/RAW_5V: J1.2 (VCC), J3.1, J4.1, Q1.3 (D)
/RS485_A: D9.1 (K), J4.3, R5.1, U2.7 (B)
/RS485_B: D9.2 (K), J4.2, R5.2, U2.6 (A)
/RS485_TXE: U1.14 (PB2), U2.2 (~RE), U2.3 (DE)
/RST: J1.5 (~RST), R19.2, U1.29 (~RESET/PC6), U3.16 (nRESET), U4.16 (nRESET), U5.16 (nRESET), U6.3 (IO2)
/SPI_MISO: J1.1 (MISO), R3.1, U1.16 (PB4), U6.4 (IO3)
/SPI_MOSI: J1.4 (MOSI), R2.1, U1.15 (PB3), U6.6 (IO4)
/SPI_SCK: J1.3 (SCK), U1.17 (PB5), U6.1 (IO1)
/STATUS: R6.1, U1.32 (PD2)
/STEP0: U1.13 (PB1), U3.22 (STEP)
/STEP1: U1.30 (PD0), U4.22 (STEP)
/STEP2: U1.31 (PD1), U5.22 (STEP)
/STEP_EN: U1.12 (PB0), U3.21 (nENBL), U4.21 (nENBL), U5.21 (nENBL)
/Stepper module/VREF: RV1.2, U3.12 (AVREF), U3.13 (BVREF), U4.12 (AVREF), U4.13 (BVREF), U5.12 (AVREF), U5.13 (BVREF)
/UART_RXD: R3.2, U2.1 (RO)
/UART_TXD: R2.2, U2.4 (DI)
/XTAL1: C11.1, U1.7 (XTAL1/PB6), Y1.1
/XTAL2: C17.1, U1.8 (XTAL2/PB7), Y1.3
GND: C1.2, C2.2, C3.2, C4.2, C5.2, C6.2, C9.2, C10.2, C11.2, C12.2, C15.2, C16.2, C17.2, C18.2, C21.2, C22.2, C24.2, C30.2, C31.2, D1.1 (K), D2.1 (K), D3.1 (K), D6.2 (A2), D7.2 (A2), D8.1 (K), D9.3 (A), J1.6 (GND), J2.2, J3.4, J4.4, Q1.1 (G), R10.2, R11.2, R13.2, R14.2, R16.2, R17.2, RV1.1, U1.5 (GND), U1.21 (GND), U2.5 (GND), U3.14 (GND), U3.28 (GND), U3.29 (PAD), U4.14 (GND), U4.28 (GND), U4.29 (PAD), U5.14 (GND), U5.28 (GND), U5.29 (PAD), U6.2 (VN), U8.2 (VN), Y1.2, Y1.4
unnamed: C3.1, C4.1, D7.1 (A1), FB2.1, Q1.2 (S)
unnamed: C5.1, C6.1, F1.1, FB1.1
unnamed: C7.1, U3.1 (CP1)
unnamed: C7.2, U3.2 (CP2)
unnamed: C8.1, R9.1, U3.3 (VCP)
unnamed: C12.1, U5.15 (V3P3OUT)
unnamed: C13.1, U4.1 (CP1)
unnamed: C13.2, U4.2 (CP2)
unnamed: C14.1, R12.1, U4.3 (VCP)
unnamed: C18.1, U3.15 (V3P3OUT)
unnamed: C19.1, U5.1 (CP1)
unnamed: C19.2, U5.2 (CP2)
unnamed: C20.1, R15.1, U5.3 (VCP)
unnamed: C24.1, U4.15 (V3P3OUT)
unnamed: D1.2 (A), R4.2
unnamed: D2.2 (A), R6.2
unnamed: D3.2 (A), R7.2
unnamed: D5.1 (K), D6.1 (A1), F1.2
unnamed: D5.2 (A), J2.1
unnamed: D8.2 (A), R1.2
unnamed: J5.1, U3.8 (BOUT2)
unnamed: J5.2, U3.10 (BOUT1)
unnamed: J5.3, U3.7 (AOUT2)
unnamed: J5.4, U3.5 (AOUT1)
unnamed: J6.1, U4.8 (BOUT2)
unnamed: J6.2, U4.10 (BOUT1)
unnamed: J6.3, U4.7 (AOUT2)
unnamed: J6.4, U4.5 (AOUT1)
unnamed: J7.1, U5.8 (BOUT2)
unnamed: J7.2, U5.10 (BOUT1)
unnamed: J7.3, U5.7 (AOUT2)
unnamed: J7.4, U5.5 (AOUT1)
unnamed: R10.1, U3.9 (ISENB)
unnamed: R11.1, U3.6 (ISENA)
unnamed: R13.1, U4.9 (ISENB)
unnamed: R14.1, U4.6 (ISENA)
unnamed: R16.1, U5.9 (ISENB)
unnamed: R17.1, U5.6 (ISENA)
unnamed: R18.2, RV1.3
